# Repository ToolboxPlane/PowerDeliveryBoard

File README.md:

View this project on [CADLAB.io](https://cadlab.io/node/755). 

# PowerDeliveryBoard

This board provides and monitors a 5V and 3.3V rail and monitors battery voltage and current.

Top Side|Bottom Side
:-------------------------:|:-------------------------:
|

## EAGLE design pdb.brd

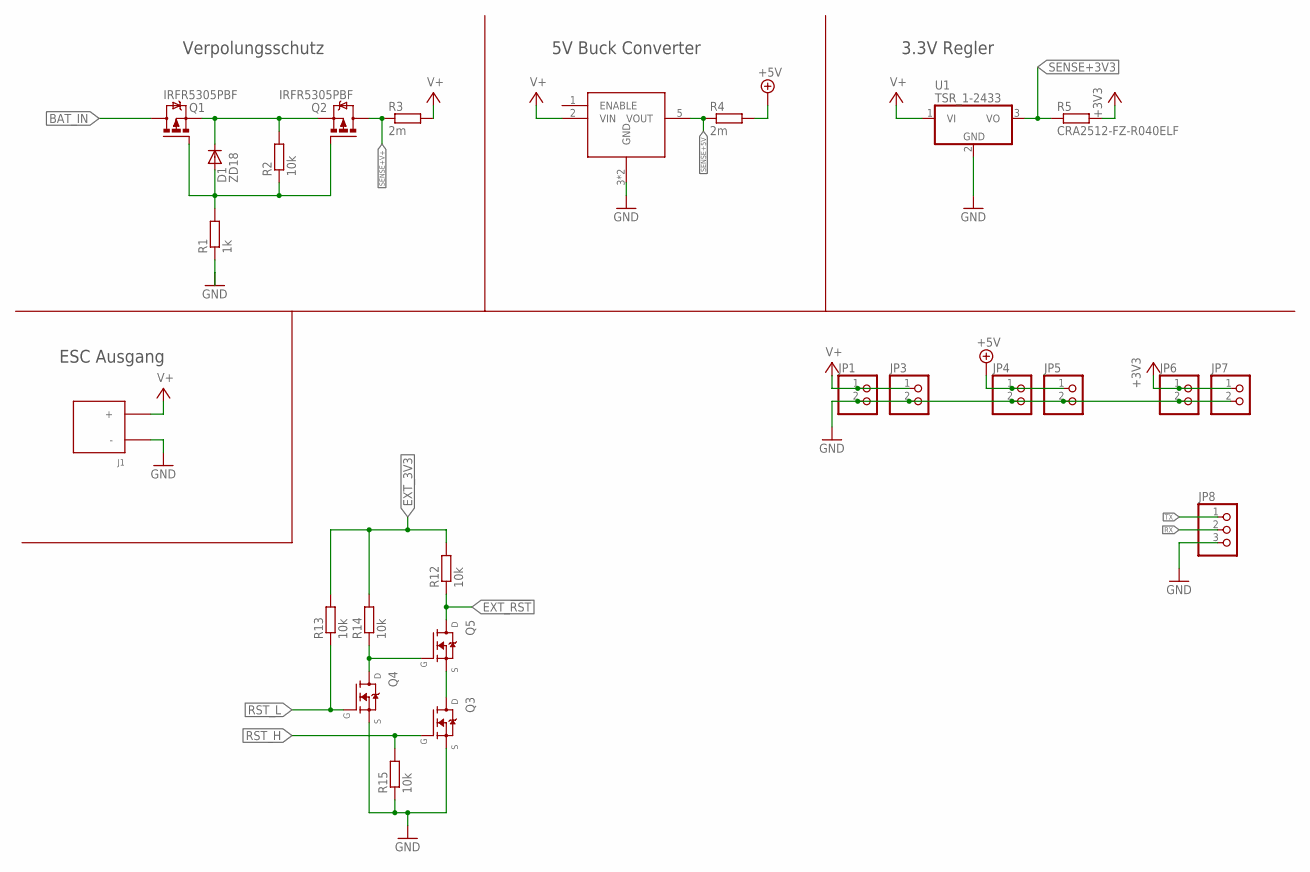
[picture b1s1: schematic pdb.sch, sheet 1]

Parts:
A1: D24V50F5SINGLESCREW; D24V50F5_SINGLESCREW
D1: ZD18; DO214BA
J1: XT60PWFEMALE
JP1, JP3, JP4, JP5, JP6, JP7: PINHD-1X2; 1X02
JP8: PINHD-1X3/90; 1X03/90
Q1, Q2: IRFR5305PBF; D-PAK_TO252AA
Q3, Q4, Q5: BSN20,215; BSN20_215
R1: 1k; R0603
R2, R12, R13, R14, R15: 10k; R0603
R3, R4: 2m; 3920
R5: CRA2512-FZ-R040ELF; BO_CRA2512
U1: TSR_1-2433; TSR-1

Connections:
+3V3: JP6.1, JP7.1, R5.2; also elsewhere on the board
+5V: JP4.1, JP5.1, R4.P$2 (2); also elsewhere on the board
AKKU-ZWISCHEN: D1.C, Q1.3 (S), Q2.3 (S), R2.2
BAT_IN: Q1.4 (D)
EXT_3V3: R12.2, R13.2, R14.2; also elsewhere on the board
EXT_!RST: Q5.3 (D), R12.1; also elsewhere on the board
GND: A1.3 (GND), A1.4 (GND), J1.NEG (-), JP1.2, JP3.2, JP4.2, JP5.2, JP6.2, JP7.2, JP8.3, Q3.2 (S), Q4.2 (S), R1.1, R15.1, U1.2 (GND); also elsewhere on the board
unnamed: Q4.3 (D), Q5.1 (G), R14.1
unnamed: Q3.3 (D), Q5.2 (S)
unnamed: D1.A, Q1.1 (G), Q2.1 (G), R1.2, R2.1
RST_H: Q3.1 (G), R15.2; also elsewhere on the board
RST_L: Q4.1 (G), R13.1; also elsewhere on the board
RX: JP8.2; also elsewhere on the board
SENSE+3V3: R5.1, U1.3 (VO); also elsewhere on the board
SENSE+5V: A1.5 (VOUT), R4.P$1 (1); also elsewhere on the board
SENSE+V+: Q2.4 (D), R3.P$1 (1); also elsewhere on the board
TX: JP8.1; also elsewhere on the board
V+: A1.2 (VIN), J1.POS (+), JP1.1, JP3.1, R3.P$2 (2), U1.1 (VI); also elsewhere on the board

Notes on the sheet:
Verpolungsschutz
5V Buck Converter
3.3V Regler
ESC Ausgang

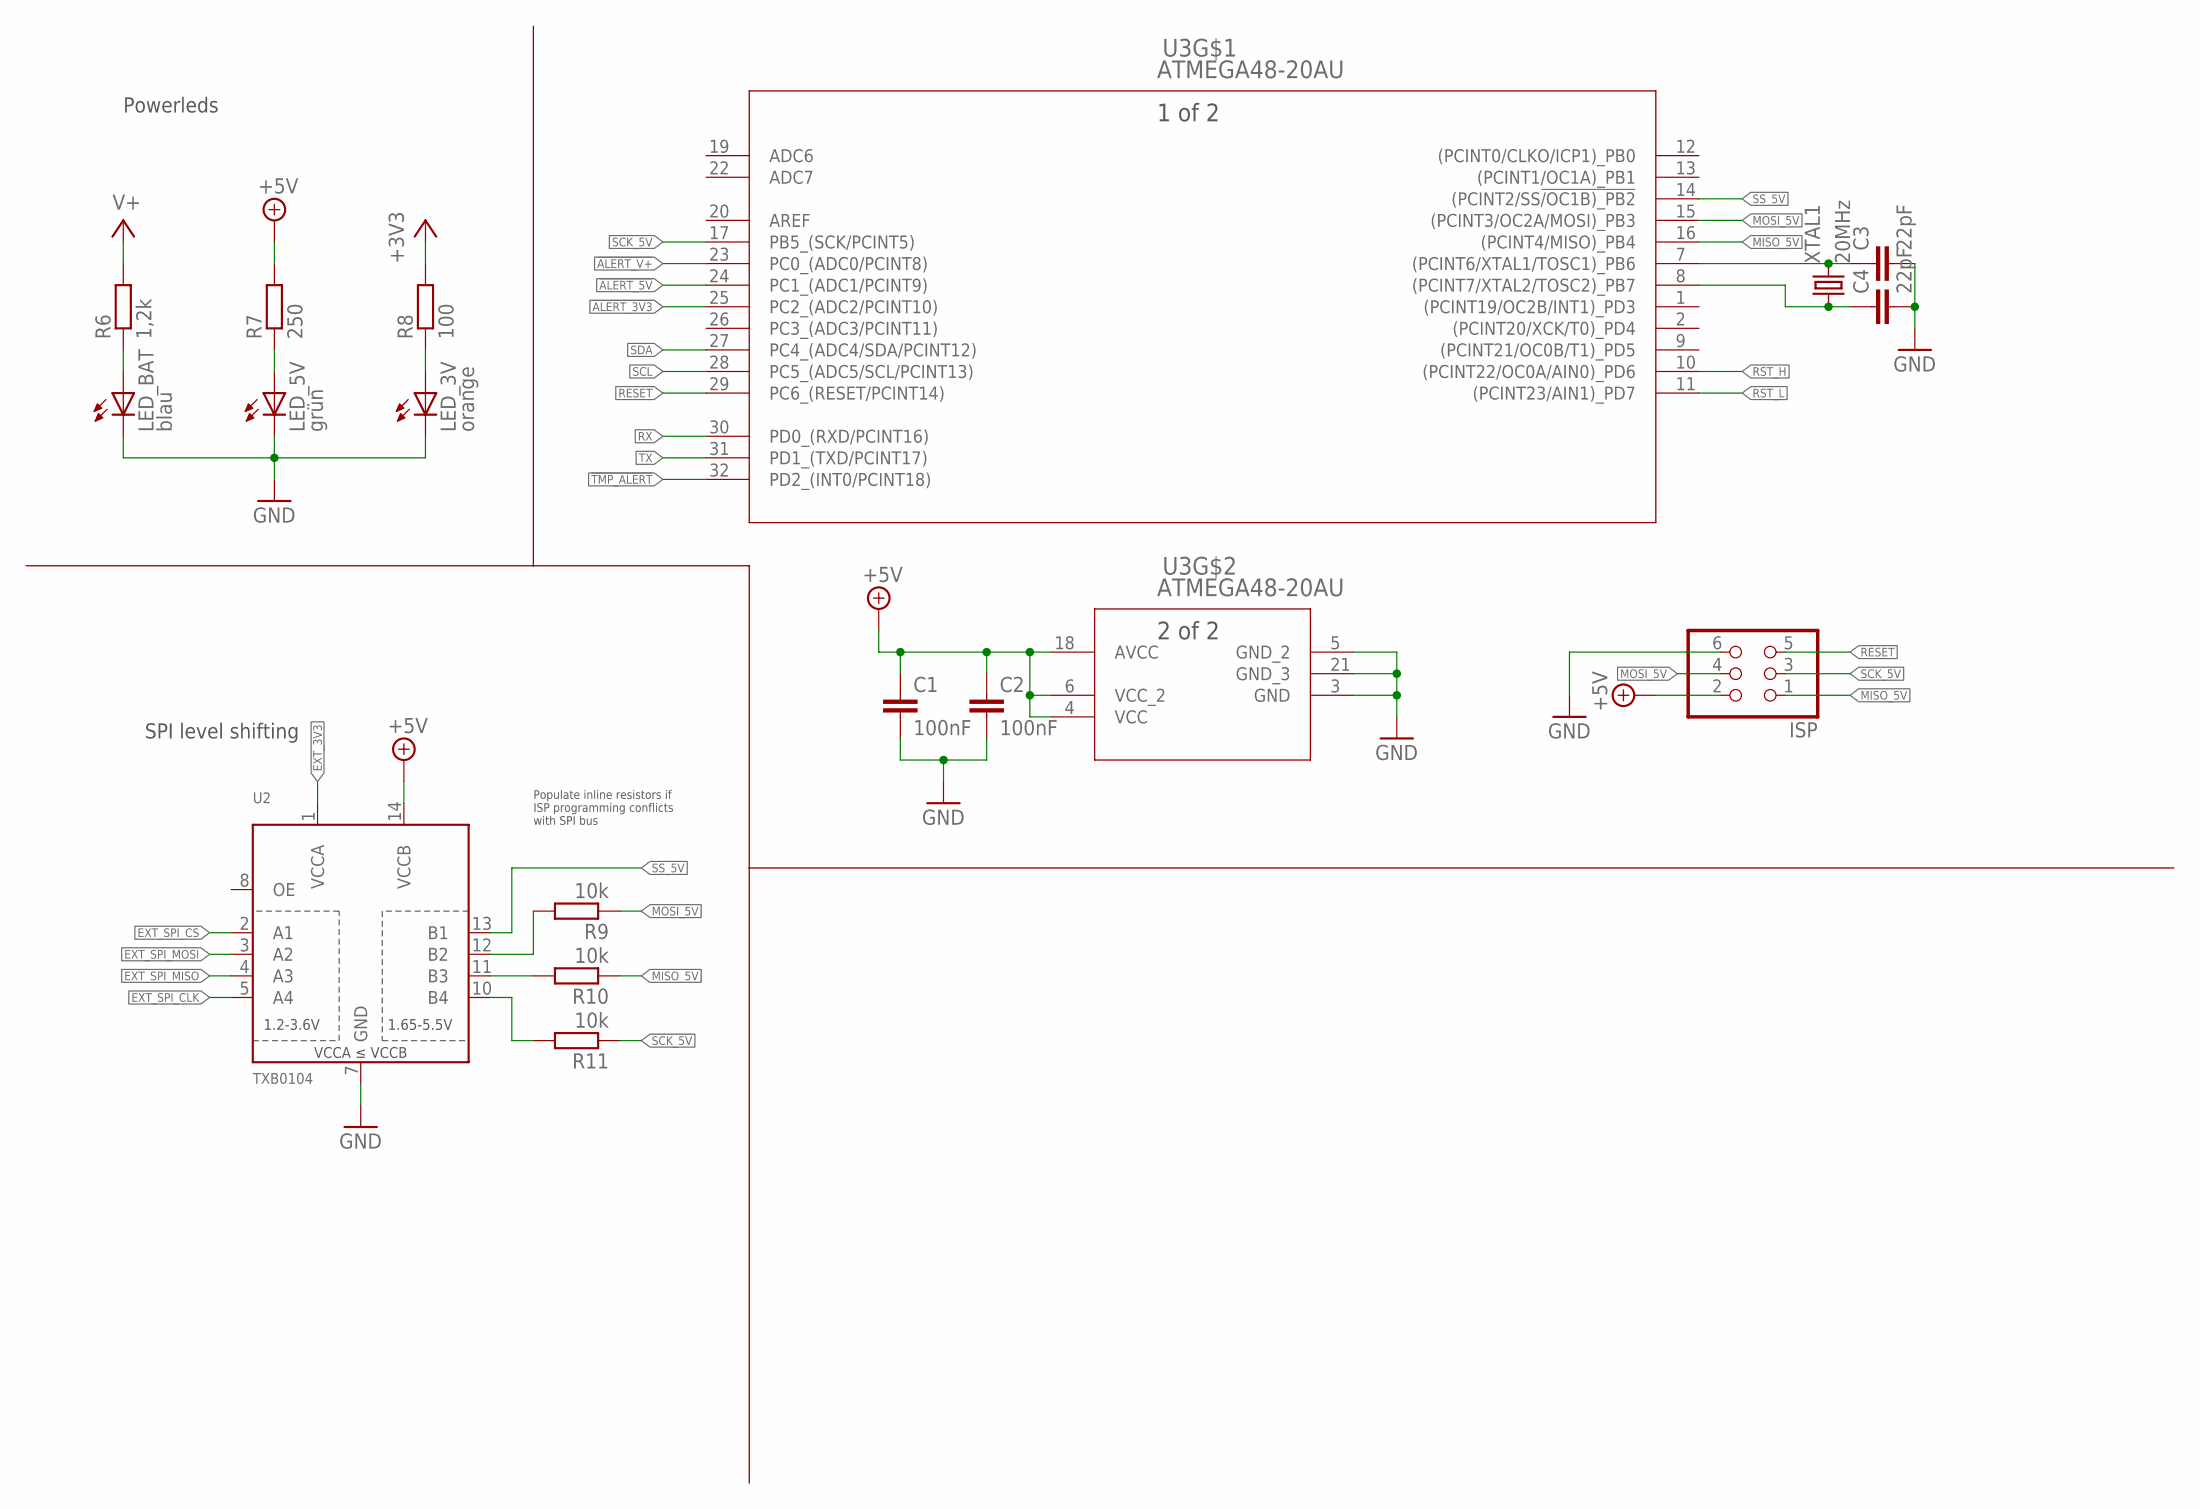
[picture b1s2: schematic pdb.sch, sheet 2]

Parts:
C1, C2: 100nF; C0603
C3, C4: 22pF; C0603
ISP: PINHD-2X3/90; 2X03/90
LED_3V: orange; CHIP-LED0603
LED_5V: grün; CHIP-LED0603
LED_BAT: blau; CHIP-LED0603
R6: 1,2k; R0603
R7: 250; R0603
R8: 100; R0603
R9, R10, R11: 10k; R0603
U2: TXB0104; SOP65P640X120-14
U3: ATMEGA48-20AU; QFP80P900X900X120-32
XTAL1: 20MHz; HC49UP

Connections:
!ALERT_3V3: U3.25 (PC2_(ADC2/PCINT10)); also elsewhere on the board
!ALERT_5V: U3.24 (PC1_(ADC1/PCINT9)); also elsewhere on the board
!ALERT_V+: U3.23 (PC0_(ADC0/PCINT8)); also elsewhere on the board
!TMP_ALERT: U3.32 (PD2_(INT0/PCINT18)); also elsewhere on the board
+3V3: R8.2; also elsewhere on the board
+5V: C1.1, C2.1, ISP.2, R7.2, U2.14 (VCCB), U3.4 (VCC), U3.6 (VCC_2), U3.18 (AVCC); also elsewhere on the board
EXT_3V3: U2.1 (VCCA); also elsewhere on the board
EXT_SPI_CLK: U2.5 (A4); also elsewhere on the board
EXT_SPI_CS: U2.2 (A1); also elsewhere on the board
EXT_SPI_MISO: U2.4 (A3); also elsewhere on the board
EXT_SPI_MOSI: U2.3 (A2); also elsewhere on the board
GND: C1.2, C2.2, C3.2, C4.2, ISP.6, LED_3V.C, LED_5V.C, LED_BAT.C, U2.7 (GND), U3.3 (GND), U3.5 (GND_2), U3.21 (GND_3); also elsewhere on the board
MISO_5V: ISP.1, R10.1, U3.16 ((PCINT4/MISO)_PB4)
MOSI_5V: ISP.4, R9.1, U3.15 ((PCINT3/OC2A/MOSI)_PB3)
unnamed: R10.2, U2.11 (B3)
unnamed: R9.2, U2.12 (B2)
unnamed: R11.2, U2.10 (B4)
unnamed: LED_BAT.A, R6.1
unnamed: LED_5V.A, R7.1
unnamed: LED_3V.A, R8.1
unnamed: C3.1, U3.7 ((PCINT6/XTAL1/TOSC1)_PB6), XTAL1.2
unnamed: C4.1, U3.8 ((PCINT7/XTAL2/TOSC2)_PB7), XTAL1.1
RESET: ISP.5, U3.29 (PC6_(RESET/PCINT14))
RST_H: U3.10 ((PCINT22/OC0A/AIN0)_PD6); also elsewhere on the board
RST_L: U3.11 ((PCINT23/AIN1)_PD7); also elsewhere on the board
RX: U3.30 (PD0_(RXD/PCINT16)); also elsewhere on the board
SCK_5V: ISP.3, R11.1, U3.17 (PB5_(SCK/PCINT5))
SCL: U3.28 (PC5_(ADC5/SCL/PCINT13)); also elsewhere on the board
SDA: U3.27 (PC4_(ADC4/SDA/PCINT12)); also elsewhere on the board
SS_5V: U2.13 (B1), U3.14 ((PCINT2/SS!/OC1B)_PB2)
TX: U3.31 (PD1_(TXD/PCINT17)); also elsewhere on the board
V+: R6.2; also elsewhere on the board

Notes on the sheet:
Powerleds
SPI level shifting
Populate inline resistors if ISP programming conflicts with SPI bus

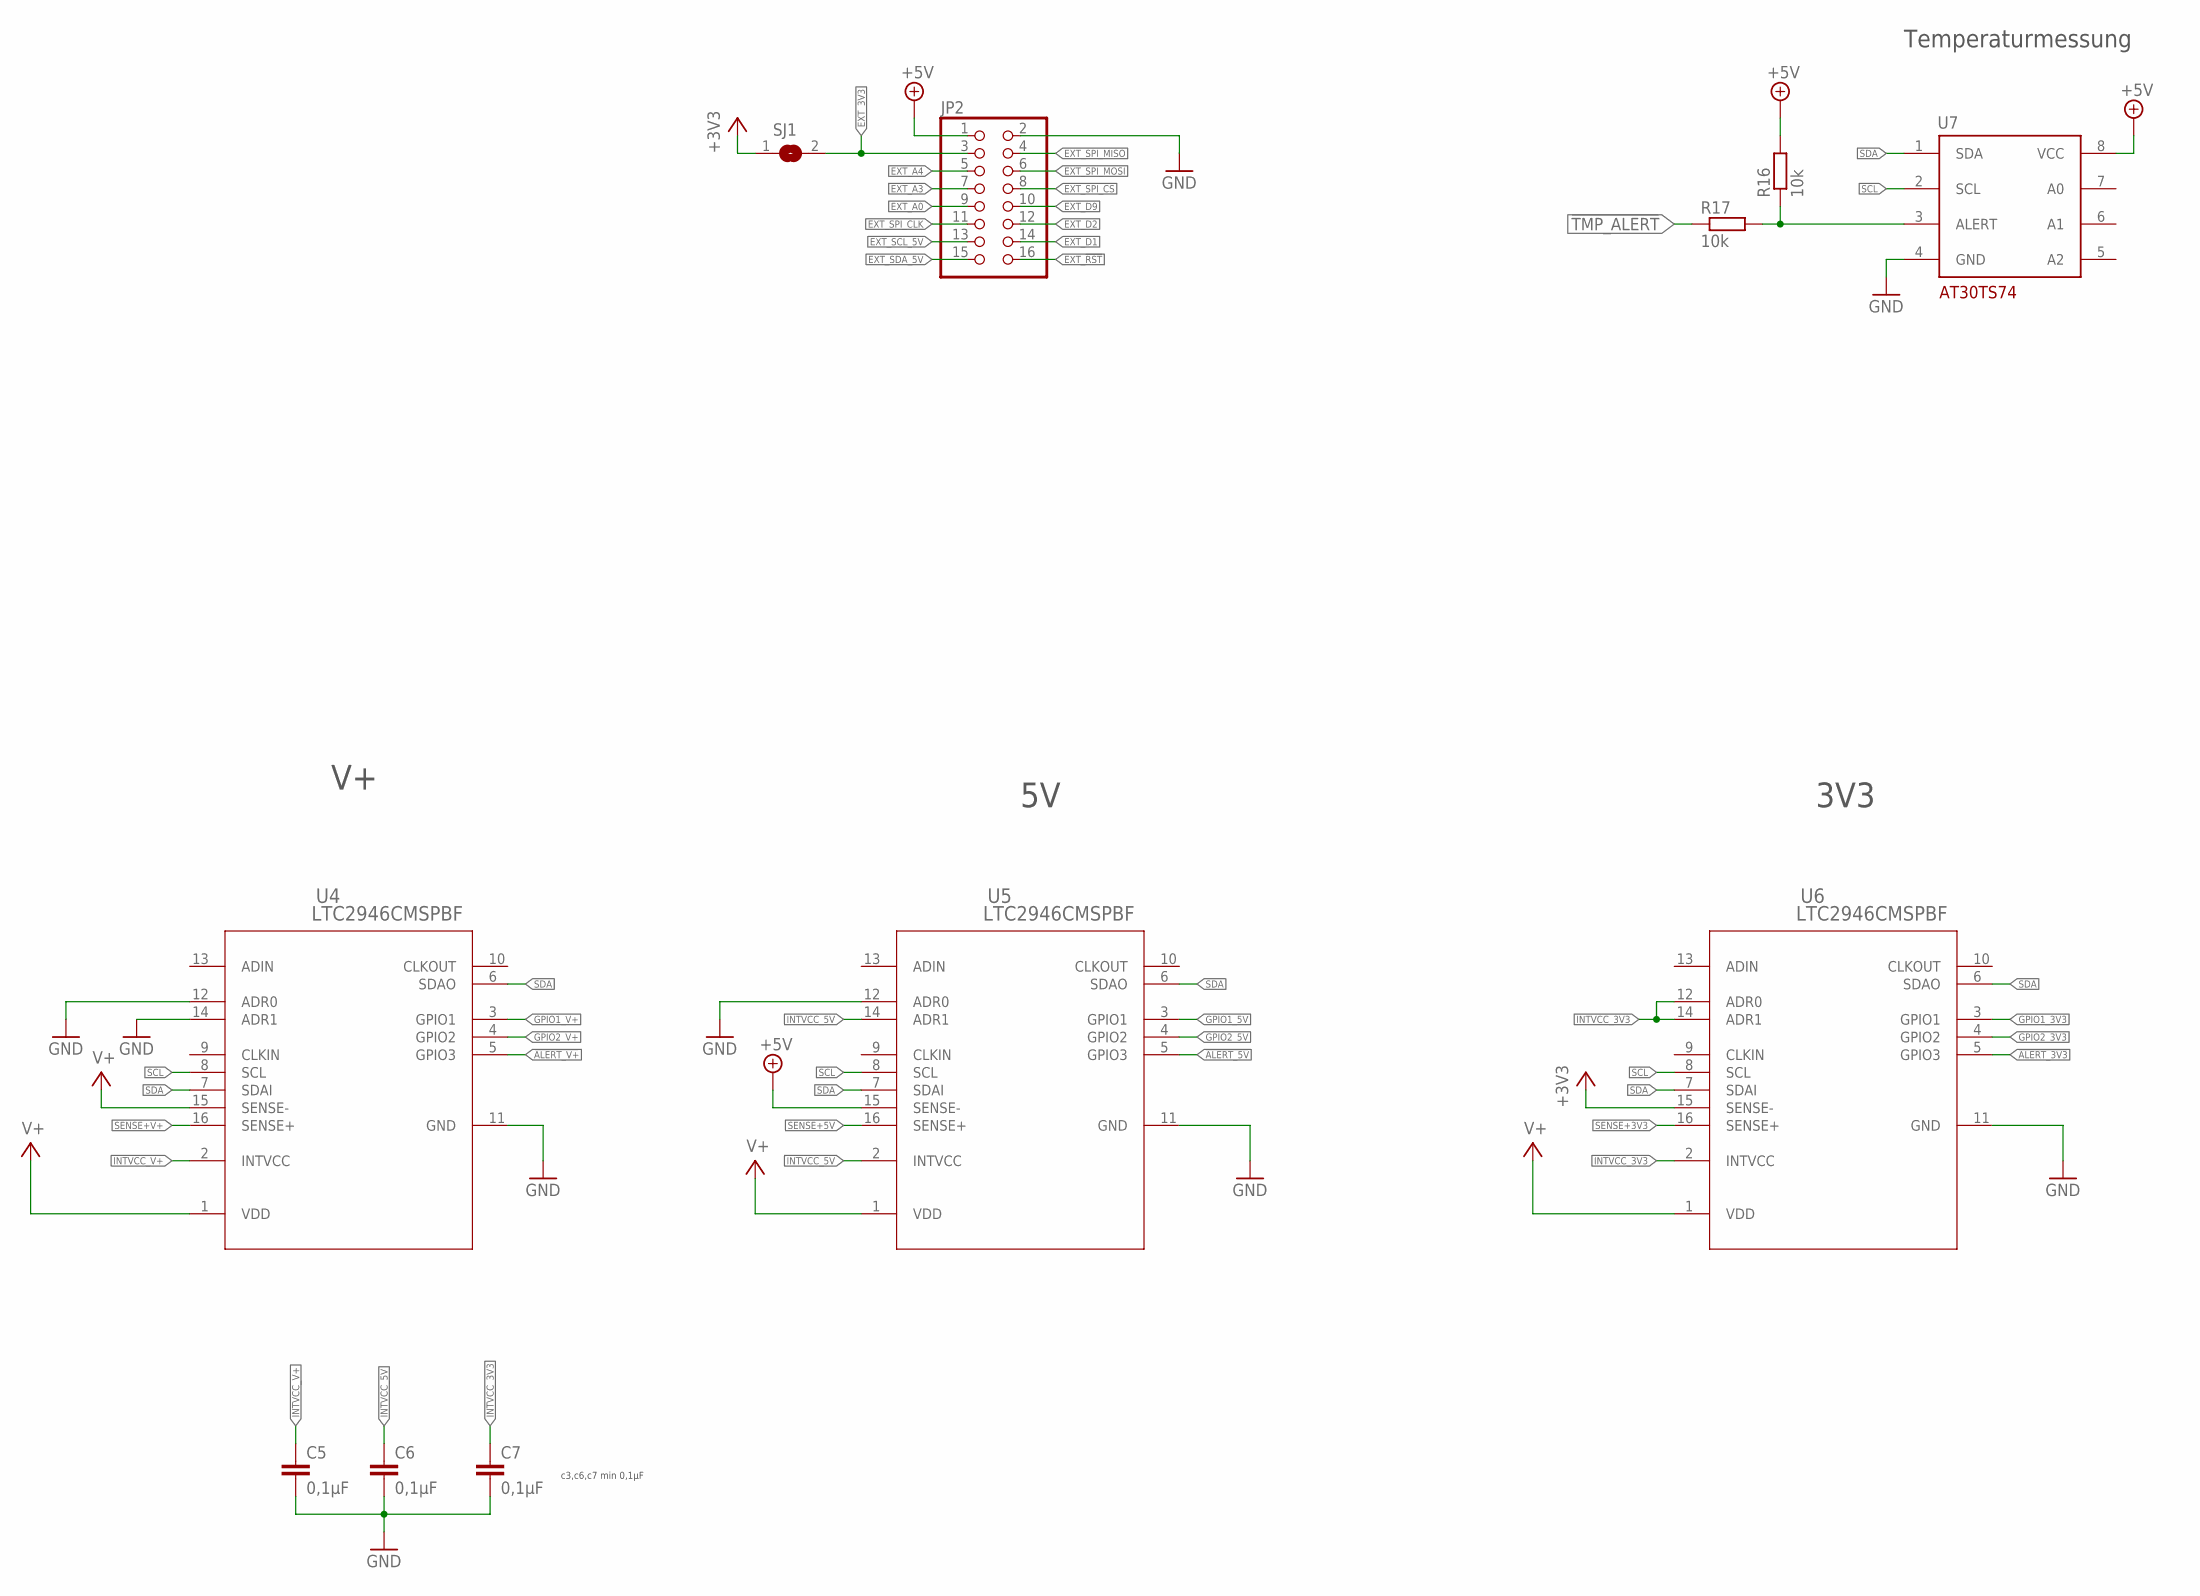
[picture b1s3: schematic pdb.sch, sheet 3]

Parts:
C5, C6, C7: 0,1µF; C0603
JP2: PINHD-2X8; 2X08
R16, R17: 10k; R0603
SJ1: SJ
U4, U5, U6: LTC2946CMSPBF; SOP50P489X110-16
U7: AT30TS74SS8M; SO08

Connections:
!ALERT_3V3: U6.5 (GPIO3); also elsewhere on the board
!ALERT_5V: U5.5 (GPIO3); also elsewhere on the board
!ALERT_V+: U4.5 (GPIO3); also elsewhere on the board
!TMP_ALERT: R17.1; also elsewhere on the board
+3V3: SJ1.1, U6.15 (SENSE-); also elsewhere on the board
+5V: JP2.1, R16.2, U5.15 (SENSE-), U7.8 (VCC); also elsewhere on the board
EXT_3V3: JP2.3, SJ1.2; also elsewhere on the board
EXT_!RST: JP2.16; also elsewhere on the board
EXT_A0: JP2.9
EXT_A3: JP2.7
EXT_A4: JP2.5
EXT_D1: JP2.14
EXT_D2: JP2.12
EXT_D9: JP2.10
EXT_SCL_5V: JP2.13
EXT_SDA_5V: JP2.15
EXT_SPI_CLK: JP2.11; also elsewhere on the board
EXT_SPI_CS: JP2.8; also elsewhere on the board
EXT_SPI_MISO: JP2.4; also elsewhere on the board
EXT_SPI_MOSI: JP2.6; also elsewhere on the board
GND: C5.2, C6.2, C7.2, JP2.2, U4.11 (GND), U4.12 (ADR0), U4.14 (ADR1), U5.11 (GND), U5.12 (ADR0), U6.11 (GND), U7.4 (GND); also elsewhere on the board
GPIO1_3V3: U6.3 (GPIO1)
GPIO1_5V: U5.3 (GPIO1)
GPIO1_V+: U4.3 (GPIO1)
GPIO2_3V3: U6.4 (GPIO2)
GPIO2_5V: U5.4 (GPIO2)
GPIO2_V+: U4.4 (GPIO2)
INTVCC_3V3: C7.1, U6.2 (INTVCC), U6.12 (ADR0), U6.14 (ADR1)
INTVCC_5V: C6.1, U5.2 (INTVCC), U5.14 (ADR1)
INTVCC_V+: C5.1, U4.2 (INTVCC)
unnamed: R16.1, R17.2, U7.3 (ALERT)
SCL: U4.8 (SCL), U5.8 (SCL), U6.8 (SCL), U7.2 (SCL); also elsewhere on the board
SDA: U4.6 (SDAO), U4.7 (SDAI), U5.6 (SDAO), U5.7 (SDAI), U6.6 (SDAO), U6.7 (SDAI), U7.1 (SDA); also elsewhere on the board
SENSE+3V3: U6.16 (SENSE+); also elsewhere on the board
SENSE+5V: U5.16 (SENSE+); also elsewhere on the board
SENSE+V+: U4.16 (SENSE+); also elsewhere on the board
V+: U4.1 (VDD), U4.15 (SENSE-), U5.1 (VDD), U6.1 (VDD); also elsewhere on the board

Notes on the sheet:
3V3
c3,c6,c7 min 0,1µF
Temperaturmessung

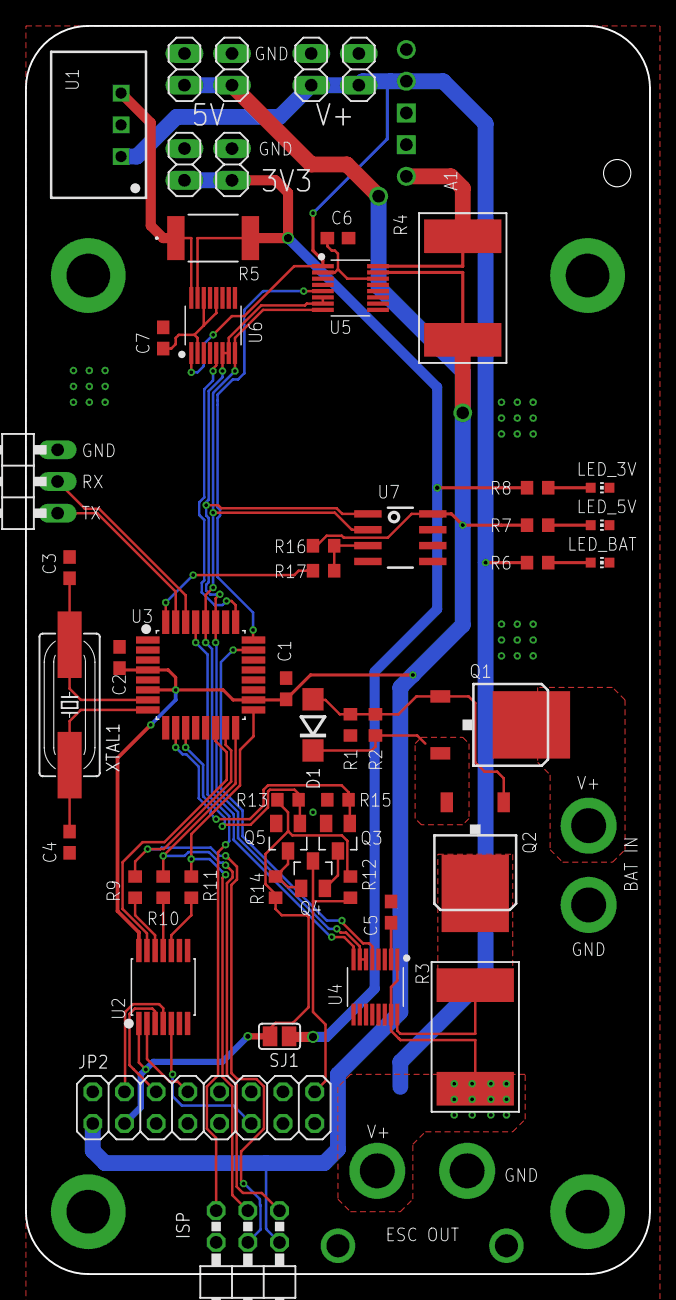
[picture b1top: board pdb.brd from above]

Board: 2 copper layers, 50.0 x 100.0 mm, 53 parts (1 on the bottom side), 44 nets.

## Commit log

2018-01-03 added gitignore
2018-01-04 Connected Levelshifter
2018-01-04 First parts placed
2018-01-04 added temperature sensor
2018-01-04 updated inductor for 3v regulator
2018-01-04 added mounting holes
2018-01-08 AT30TS74 connected
2018-01-09 Header connected, First Layout attempt
2018-01-09 5v nearly completely connected
2018-01-11 First Layout GND not connected because of wrong design rules
2018-01-12 fixed spi level shifting
2018-01-15 First Version, nearly completed
2018-01-22 added net classes
2018-01-22 assigned net classes
2018-01-22 fixed some signal trace widths
2018-01-23 ISP, SPI, I2C Bus layout
2018-01-23 added shunts
2018-01-24 fixed xt60, updated libs
2018-01-24 more wip
2018-01-26 changed R6
2018-01-30 fixed shunt resistor libraries
2018-01-30 fixed #5
2018-01-30 fixed vbat routing for better ground path
2018-01-30 fixed shunt resistor value
2018-01-30 design rules
2018-02-01 fixed min drill
2018-02-09 various improvements/fixes
    added power output pins
    fixed design rules
    moved ESC out to bottom
    fixed packages
    removed unnecessary filtering for atmega
    etc
2018-02-09 fixed #10
    removed expansion port connections
    rotated expansion port
    connected expansion port
    added 3V3 jumper
2018-02-09 changed atmega routing
2018-02-09 fixed via stop limit
2018-02-09 added images
2018-02-14 various changes
    removed netclasses, might add them later again, creates issues with sense lines
    fixed output pin
    version bump
    fixed some vias/drills
2018-02-14 gnd routing
    netclasses
2018-02-23 sachen gemacht dass fusion glücklich ist
2018-02-23 layout stuff
2018-02-24 multiple changes
    removed inductor,
    fixed layout + schematic
2018-03-09 Backlink to CADLAB.io has been added.
2018-03-11 various changes
    moved smd components on metric grid
    silkscreen, reduced fuckup in part sizes
    added output
2018-03-12 fixed 3d models
2018-03-12 added reset, closed #11
2018-03-12 silkscreen
2018-03-12 fixed layout, silkscreen, resistor values
2018-03-12 changed LTC2946 for easier soldering
2018-03-12 fixed atmega
    closes #12
2018-03-12 fixed naming, silkscreen
2018-03-12 silkscreen fixes
2018-03-12 added temperature alert
2018-03-12 added serial port
2018-03-12 fixed silkscreen: jp8
2018-03-12 fixed gnd routing
2018-03-12 fixed levelshifter footprint
2018-03-12 R value levelshifter
2018-03-12 ti lib update
2018-03-13 improved high current traces
2018-03-13 removed unnecessary gnd traces
2018-03-14 fixed typo
2018-03-14 Update README.md
    fixed cadlab link
2018-03-15 updated pictures in readme
2018-08-14 adds LMZ13608 lbr
2018-08-14 remove old schematic
2018-08-14 adds new empty schematic
2018-08-14 adds frame
2018-08-14 adds LMZ13608 and resistors to set output voltage
2018-08-16 Cin, formatting
2018-08-16 Cin, formatting
    not only the library file this time
2018-08-19 added ATmega2560 library
2018-08-22 added ATmega
    + crystal, ISP
2018-08-22 adds FT230X
2018-08-22 fix atmega supply voltage
    fixes #26
2018-08-22 adds LTC2946 library
2018-08-22 adds shunt_resistor lbr
2018-08-22 adds power monitoring
2018-08-22 adds 4 programmable LEDs on PL0-PL3
2018-08-30 moved *.lbr to LBR directory
2018-08-30 adds micromatch lbr
2018-08-30 adds expansion port
2018-08-30 adds lbr to gitignore
2018-09-02 3.3v regulation
2018-09-03 adds missing schottky diode for 3.3v reg
    fixes #30
2018-09-04 adds XT60
2018-09-08 adds FlightComputer USB connector
2019-01-05 kicad
2019-01-05 adds submodules
2019-02-22 assign vbat shunt footprint
2019-02-22 LMZ13608 input caps
2019-02-22 fix missing footprint
2019-02-22 LMZ13608 output caps
2019-02-22 5V shunt
2019-02-23 fix footprints
2019-02-23 fix serial connection ftdi-atmega
2019-02-23 update ottojo lib
2019-02-25 update xt60
2019-02-27 update footprints
2019-03-03 move FT230 to https://github.com/ToolboxPlane/FT230Module
2019-03-12 smaller shunt on 5v rail
2019-03-12 LMZ13608 3d model
2019-03-12 add rx/tx labels
2019-03-12 annotate parts
2019-03-12 update USB footprint
2019-03-13 add 3d model for USB-C
2019-03-13 update USB C footprint
2019-03-13 add XT30 5V Out
2019-03-13 3v3 regulator 3d model
2019-03-13 USB C Power Port
2019-03-13 layout WIP
2019-03-19 update submodule for USBC
2019-04-03 wip und so
2019-04-03 add fp-info-cache to gitignore
2019-04-03 add reset switch
2019-04-03 LMZM23600 from kicad libs
2019-04-04 remove isolation from FT230
2019-04-04 more LEDs
2019-04-04 layout
2019-04-05 more layout
2019-04-05 even more layout
2019-04-05 layout fixes, reannotate
2019-04-05 silkscreen stuff
2019-04-05 the ACTUAL silkscreen stuff, including the actual changes this time
2019-04-05 use official XT30 footprint
2019-04-05 rounded corners
2019-04-05 add missing trace near USB
2019-04-07 mounting dimensions
2019-04-07 oshw logo
2019-04-07 rebuild zones
2019-04-07 fix 3.3v regulator output cap
2019-04-07 fix thermals for 5V out
2019-04-07 layout fixes
2019-04-07 add large toolbox logo on bottom side
2019-04-27 fix LEDs
2019-04-27 fix debug LED resistors
